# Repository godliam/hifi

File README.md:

# Hack实验室 HiFi耳放
原作者: Hack实验室 apollo  
Forked from: [hack-apollo](https://github.com/hack-apollo)  

## Bug fix: 
### V1.3: 
- 修复了左右声道相反的问题
    - 优化了6.35mm元件库图，使其更接近真实情况
    - 修正了主工程原理图
    - 修正了主工程中输出至6.35mm耳机接口的线路，重新生成了Geber
    - 修正了后面板左右声道标志，重新生成后面板Geber

By: godliam 2022.01.25

## License
Hack Audio Spectrum is a free download and may be used, modified, evaluated and distributed without charge provided the user adheres to version three of the GNU General Public License (GPL) and does not remove the copyright notice or this text. The GPL V3 text is available on the gnu.org web site.

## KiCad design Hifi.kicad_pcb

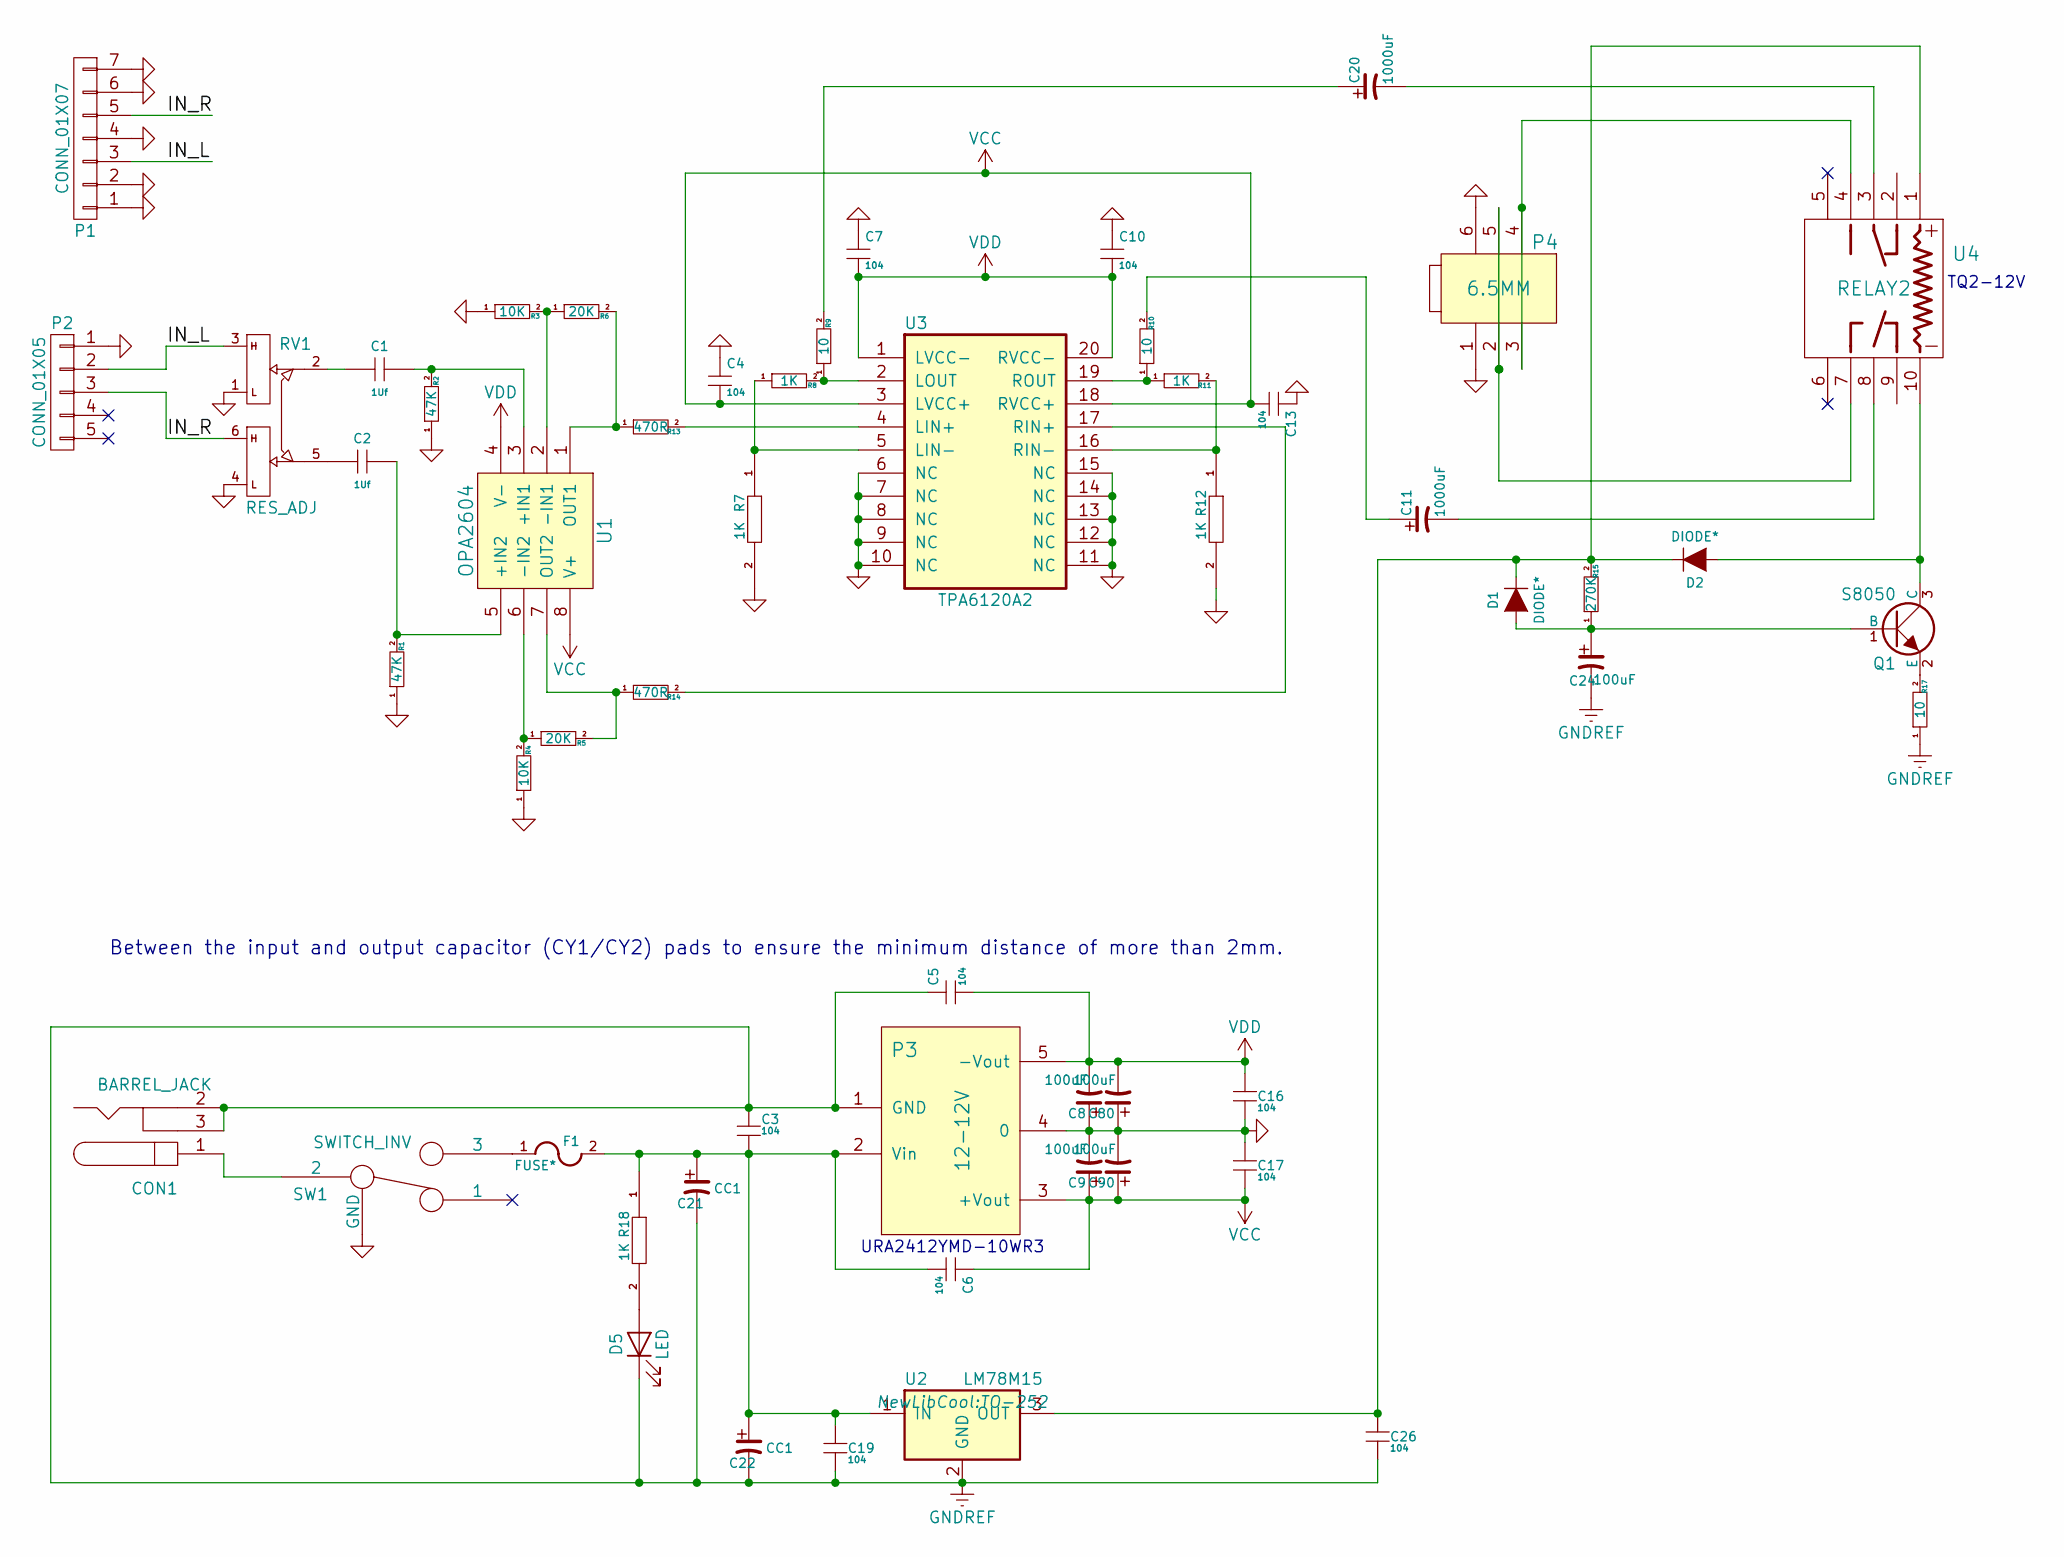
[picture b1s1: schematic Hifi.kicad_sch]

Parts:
C1, C2: 1Uf; CP_Radial_D5.0mm_P2.50mm
C3, C4, C5, C6, C7, C10, C13, C16, C17, C19, C26: 104; 0805_C
C8, C9, C24, C80, C90: 100uF; c_elec_8x10.5
C11, C20: 1000uF; TantalC_SizeT_3528
C21, C22: CC1; c_elec_8x10.5
CON1: BARREL_JACK; DCDCJACK_ALIM
D1, D2: DIODE*; DO-Diode-214BA
D5: LED; LED-3MM
F1: FUSE*; F_1812
P1: CONN_01X07; Audio_LianHua
P2: CONN_01X05; Audio_3.5mm
P3: 12-12V; DC-DC
P4: 6.5MM; Audio_6.35mm_CN
Q1: S8050; TO-92
R1, R2: 47K; 0805_R
R3, R4: 10K; 0805_R
R5, R6: 20K; 0805_R
R7, R8, R11, R12, R18: 1K; 0805_R
R9, R10, R17: 10; 0805_R
R13, R14: 470R; 0805_R
R15: 270K; 0805_R
RV1: RES_ADJ; ADJ_RES
SW1: SWITCH_INV; SWITCH_Toggle
U1: OPA2604; DIP-8_NEW
U2: LM78M15; TO-252
U3: TPA6120A2; SOIC-20_7.5x12.8mm_Pitch1.27mm
U4: RELAY2; RELAY_A5W

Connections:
/IN_L: P1.3, P2.2, RV1.3
/IN_R: P1.5, P2.3, RV1.6
GND: C4.1, C7.1, C8.1, C9.2, C10.1, C13.1, C16.2, C17.1, C80.1, C90.2, P1.1, P1.2, P1.4, P1.6, P1.7, P2.1, P3.4 (0), P4.1, P4.6, R1.1, R2.1, R3.1, R4.1, R7.2, R12.2, RV1.1, RV1.4, SW1.0 (GND), U3.6 (NC), U3.7 (NC), U3.8 (NC), U3.9 (NC), U3.10 (NC), U3.11 (NC), U3.12 (NC), U3.13 (NC), U3.14 (NC), U3.15 (NC)
GNDREF: C3.1, C5.1, C19.2, C21.2, C22.2, C24.2, C26.2, CON1.2, CON1.3, D5.1 (K), P3.1 (GND), R17.1, U2.2 (GND)
unnamed: C1.1, RV1.2
unnamed: C1.2, R2.2, U1.3 (+IN1)
unnamed: C2.1, RV1.5
unnamed: C2.2, R1.2, U1.5 (+IN2)
unnamed: C11.1, R10.2
unnamed: C11.2, U4.8
unnamed: C3.2, C6.2, C19.1, C21.1, C22.1, F1.2, P3.2 (Vin), R18.1, U2.1 (IN)
unnamed: C20.1, R9.2
unnamed: C20.2, U4.3
unnamed: C24.1, D1.1 (A), Q1.1 (B), R15.1
unnamed: C26.1, D1.2 (K), D2.2 (K), R15.2, U2.3 (OUT), U4.1
unnamed: CON1.1, SW1.2
unnamed: D2.1 (A), Q1.3 (C), U4.10
unnamed: D5.2 (A), R18.2
unnamed: F1.1, SW1.3
unnamed: P4.2, P4.5, U4.7
unnamed: P4.3, P4.4, U4.4
unnamed: Q1.2 (E), R17.2
unnamed: R3.2, R6.1, U1.2 (-IN1)
unnamed: R4.2, R5.1, U1.6 (-IN2)
unnamed: R7.1, R8.1, U3.5 (LIN-)
unnamed: R8.2, R9.1, U3.2 (LOUT)
unnamed: R10.1, R11.1, U3.19 (ROUT)
unnamed: R11.2, R12.1, U3.16 (RIN-)
unnamed: R6.2, R13.1, U1.1 (OUT1)
unnamed: R13.2, U3.4 (LIN+)
unnamed: R5.2, R14.1, U1.7 (OUT2)
unnamed: R14.2, U3.17 (RIN+)
VCC: C4.2, C6.1, C9.1, C13.2, C17.2, C90.1, P3.3 (+Vout), U1.8 (V+), U3.3 (LVCC+), U3.18 (RVCC+)
VDD: C5.2, C7.2, C8.2, C10.2, C16.1, C80.2, P3.5 (-Vout), U1.4 (V-), U3.1 (LVCC-), U3.20 (RVCC-)

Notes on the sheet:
URA2412YMD-10WR3
TQ2-12V
Between the input and output capacitor (CY1/CY2) pads to ensure the minimum distance of more than 2mm.

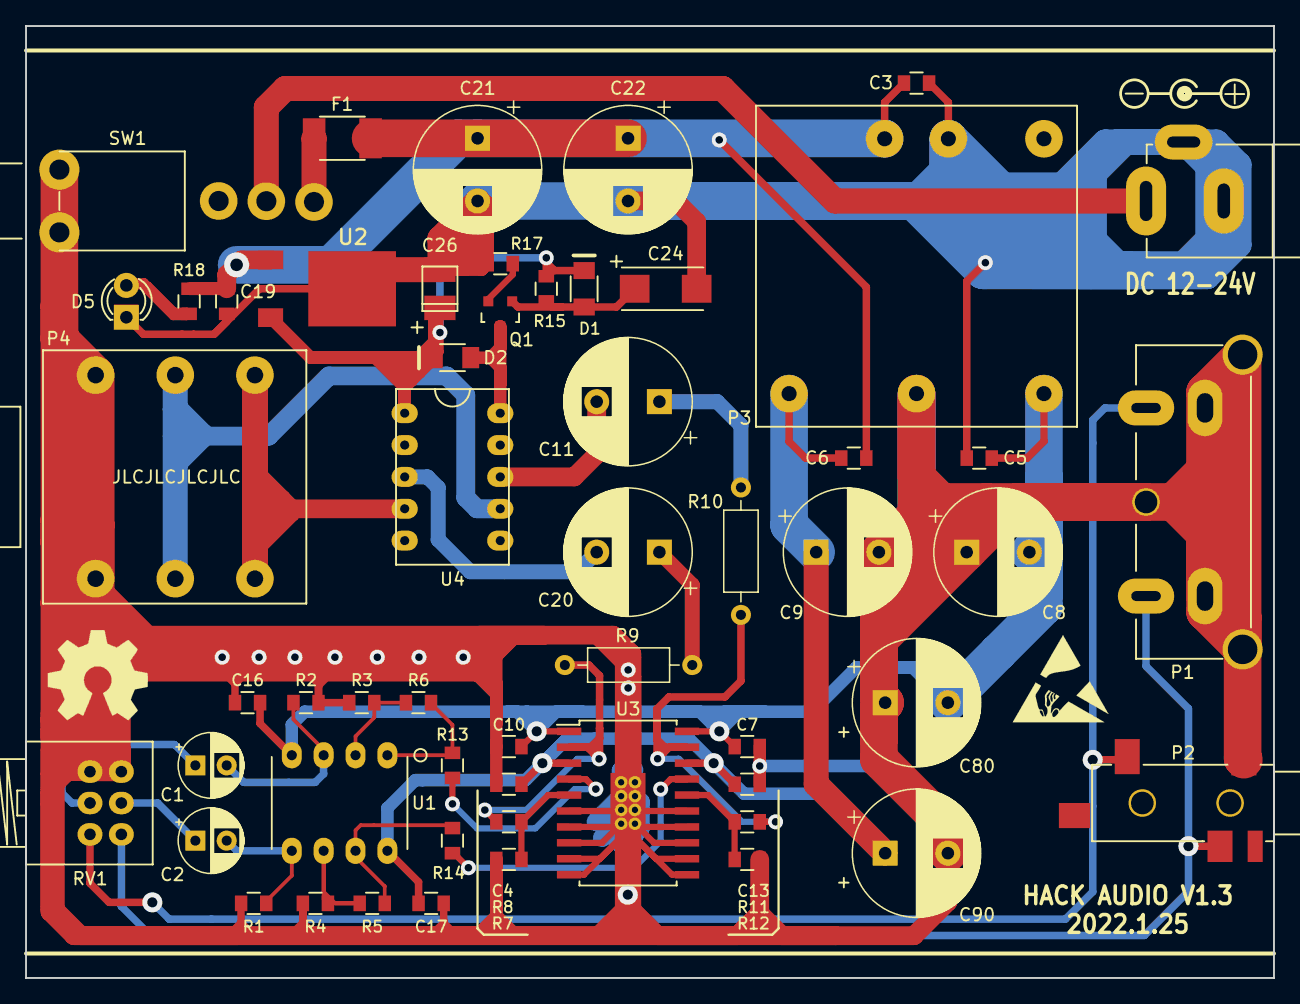
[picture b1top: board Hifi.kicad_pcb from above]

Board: 2 copper layers, 99.5 x 75.9 mm, 55 parts (0 on the bottom side), 34 nets.

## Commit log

2022-01-25 1st commit
2022-01-25 Update .gitignore
    ignore mac os temp files
2022-01-25 remove mac os temp files.
2022-03-14 License
    License
